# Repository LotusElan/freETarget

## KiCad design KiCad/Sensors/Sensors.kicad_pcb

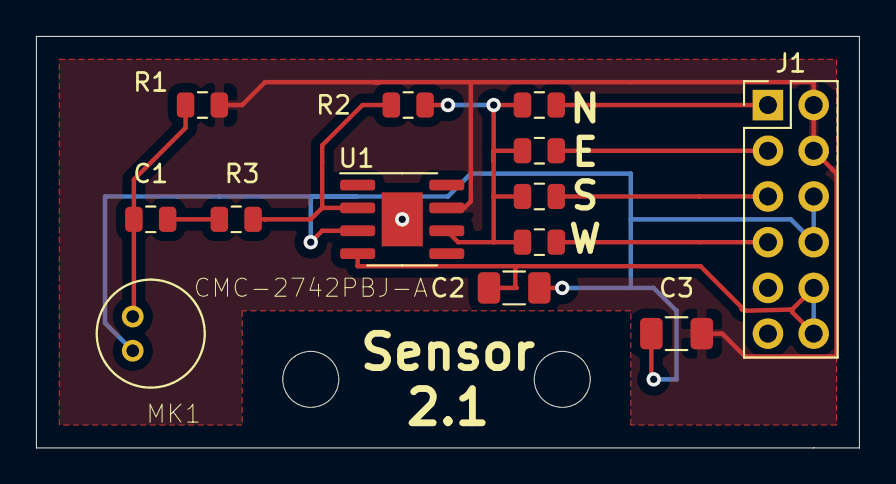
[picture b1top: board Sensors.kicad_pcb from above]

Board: 2 copper layers, 45.7 x 22.9 mm, 13 parts (0 on the bottom side), 11 nets.

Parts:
C1: 22pf; R_0805_2012Metric
C2, C3: 10u0; R_1206_3216Metric
J1: BERG 2x6; PinHeader_2x06_P2.54mm_Vertical
MK1: CMC-2742PBJ-A; CUI_CMC-2742PBJ-A
R1: 2k2; R_0805_2012Metric
R2: 10K0; R_0805_2012Metric
R3, R4, R5, R6, R7: 0r; R_0805_2012Metric
U1: OPA1641; SOIC-8-1EP_3.9x4.9mm_P1.27mm_EP2.29x3mm

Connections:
GND: C2.1, C3.2, J1.6, J1.8, MK1.GND, U1.3
unnamed: C2.2, J1.10, J1.12, U1.4
unnamed: C1.1, R3.2
unnamed: C1.2, MK1.OUT, R1.2
unnamed: J1.1, R4.1
unnamed: J1.3, R5.1
unnamed: J1.5, R6.1
unnamed: J1.7, R7.1
unnamed: R2.1, R4.2, R5.2, R6.2, R7.2, U1.6
unnamed: R2.2, R3.1, U1.2
VCC: C3.1, J1.2, J1.4, R1.1, U1.7

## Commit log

2020-07-25 In Progress for board debugging
    Issue with East Sensor being investigated
